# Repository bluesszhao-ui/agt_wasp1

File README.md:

# wasp1

wasp1 is a minimal single-core RV32I + Zicsr SoC project.

The hardware is implemented in synthesizable SystemVerilog and follows
Rocket Chip-like high-level module boundaries while using AHB-Lite as the SoC
interconnect.

## Baseline

```text
ISA: RV32I + Zicsr
Privilege: Machine mode only
MMU/TLB/PTW: none
RTL: SystemVerilog, .sv suffix
SoC bus: AHB-Lite
Core/cache internal interface: lightweight valid/ready request-response
Core plan: simple 3-stage pipeline
I-cache: direct-mapped, 16-byte line
D-cache: direct-mapped, 16-byte line, write-through
Debug target: RISC-V External Debug Spec 0.13.x / OpenOCD / GDB
Final debug probe: FT2232H-based external hardware debugger
Program storage: executable OTP
Compiler work: LLVM-based bare-metal wasp1 toolchain and BSP
```

## Top-Level Modules

```text
common
wasp1
tile
core
frontend
icache
dcache
bus
otp
sram
dma
debug
timer
intc
wdg
uart
i2c
gpio
llvm_s1
ftdi_debugger
```

Each hardware module owns its own `rtl/`, `tb/`, `filelists/`, `docs/`,
`build/`, `logs/`, `wave/`, and `Makefile` directories.
`ftdi_debugger` is not chip RTL; it owns the external FTDI debugger hardware,
OpenOCD, and board bring-up collateral.

## Current Status

Implemented and verified:

```text
common
bus
sram
otp
timer
gpio
uart
dma
intc
core
frontend
icache
dcache
tile
debug leaf blocks
wdg
i2c
wasp1 top integration smoke
```

Current residual scope:

```text
debug integration:
  true DPC/DCSR capture, single-step, breakpoints, abstract memory access

external debugger:
  FT2232H hardware debugger schematic/PCB, OpenOCD config, FPGA/board bring-up

software/toolchain:
  llvm_s1 BSP, linker script, startup code, runtime, examples, tests

full-system validation:
  interrupt-driven firmware, longer generated-image boot/DMA/programming
  regressions
```

See [ROADMAP.md](ROADMAP.md) for the live progress list and next steps.

## Quick Commands

Run all currently wired lint targets:

```sh
make lint
```

Run all currently wired module simulations:

```sh
make sim
```

Run common lint only:

```sh
make -C common lint
```

Generated build, log, and waveform outputs are ignored by git.

## Documentation

Start here:

```text
docs/index.md
```

Important project documents:

```text
ROADMAP.md
docs/wasp1_architecture.md
docs/wasp1_module_hierarchy.md
docs/wasp1_memory_map.md
docs/wasp1_design_plan.md
docs/wasp1_verification_plan.md
docs/wasp1_debug_strategy.md
docs/wasp1_otp_boot_strategy.md
docs/wasp1_llvm_s1_plan.md
docs/wasp1_implementation_targets.md
docs/wasp1_documentation_policy.md
docs/wasp1_omnigraffle_diagram_policy.md
```

## Contributor and Agent Rules

Human contributor guidance:

```text
CONTRIBUTING.md
```

Agent workflow rules:

```text
AGENTS.md
```

## License

wasp1 is licensed under the Apache License, Version 2.0. See [LICENSE](LICENSE).

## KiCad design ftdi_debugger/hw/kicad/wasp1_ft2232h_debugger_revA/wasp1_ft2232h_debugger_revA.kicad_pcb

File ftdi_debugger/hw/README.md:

# ftdi_debugger Hardware

This directory holds the FTDI debugger hardware collateral:

```text
schematic source
schematic PDF
PCB layout
gerbers
BOM
assembly notes
bring-up notes
```

The checked-in Rev A source package is:

```text
kicad/wasp1_ft2232h_debugger_revA/wasp1_ft2232h_debugger_revA.kicad_sch
schematic/wasp1_ft2232h_debugger_revA_schematic.md
schematic/wasp1_ft2232h_debugger_revA.pdf
schematic/svg/
netlist/wasp1_ft2232h_debugger_revA_nets.csv
bom/wasp1_ft2232h_debugger_revA_bom.csv
```

Its detailed electrical design and editable architecture diagram are:

```text
../docs/ftdi_debugger_revA_design_spec.md
../docs/diagrams/ftdi_debugger_revA_block.graffle
```

The native four-sheet KiCad hierarchy passes KiCad 10 ERC with zero errors and
zero warnings. The four-layer board is fully routed and its final DRC has zero
errors, zero unconnected pads, and zero schematic parity errors. Generated
manufacturing data remains under `build/manufacturing/`; fabrication and
assembly requirements are tracked in `fabrication/` and `assembly/`.

The PDF is a stable five-page A3 review preview assembled from individually
rendered sheets. The native KiCad hierarchy remains the electrical source of
truth; SVG exports provide vector page review.

The first schematic revision must follow:

```text
../docs/ftdi_debugger_pinout.md
../openocd/wasp1_ft2232h_reference.cfg
```

Before PCB work, keep the schematic pin mapping, target connector silk, and
OpenOCD layout masks synchronized. The repository-level static check is:

```text
make -C ftdi_debugger lint
```

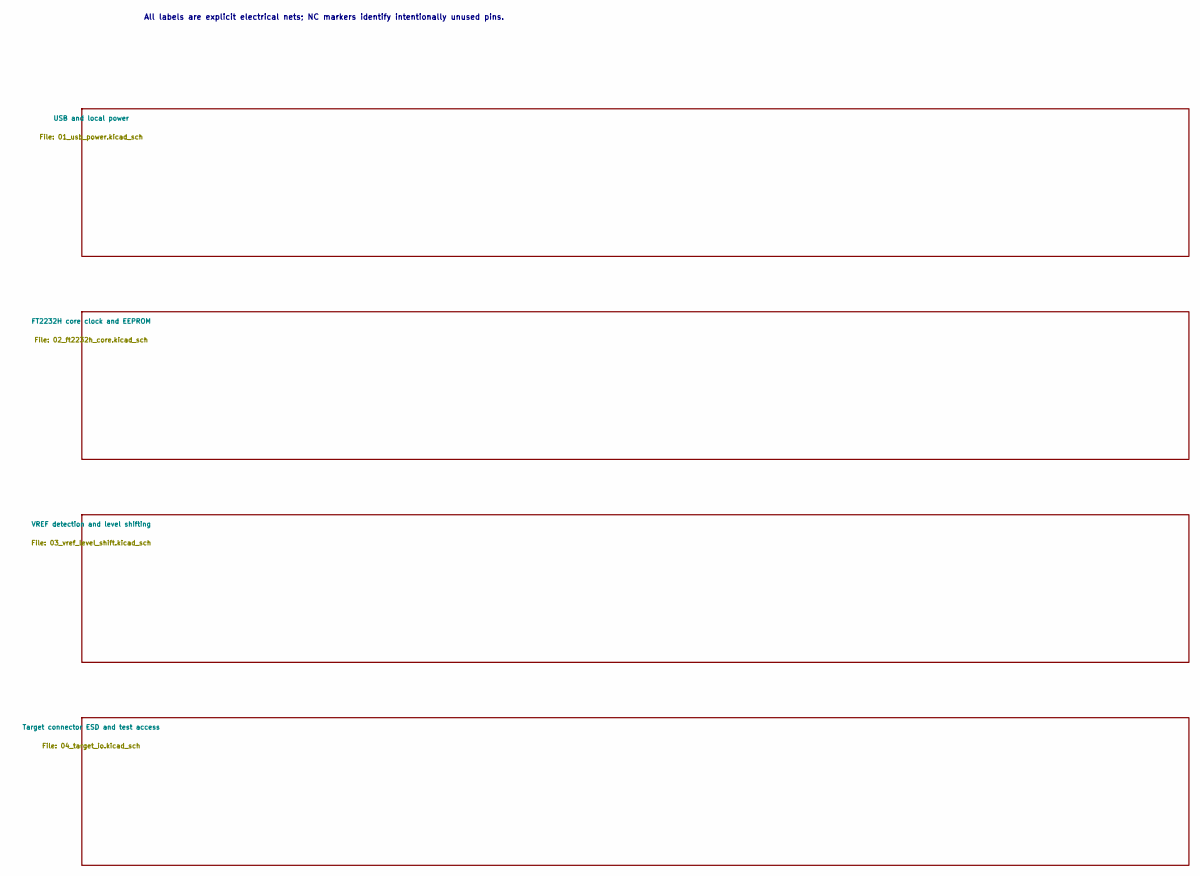
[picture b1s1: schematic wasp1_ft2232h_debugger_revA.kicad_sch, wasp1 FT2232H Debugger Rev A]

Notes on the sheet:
All labels are explicit electrical nets; NC markers identify intentionally unused pins.

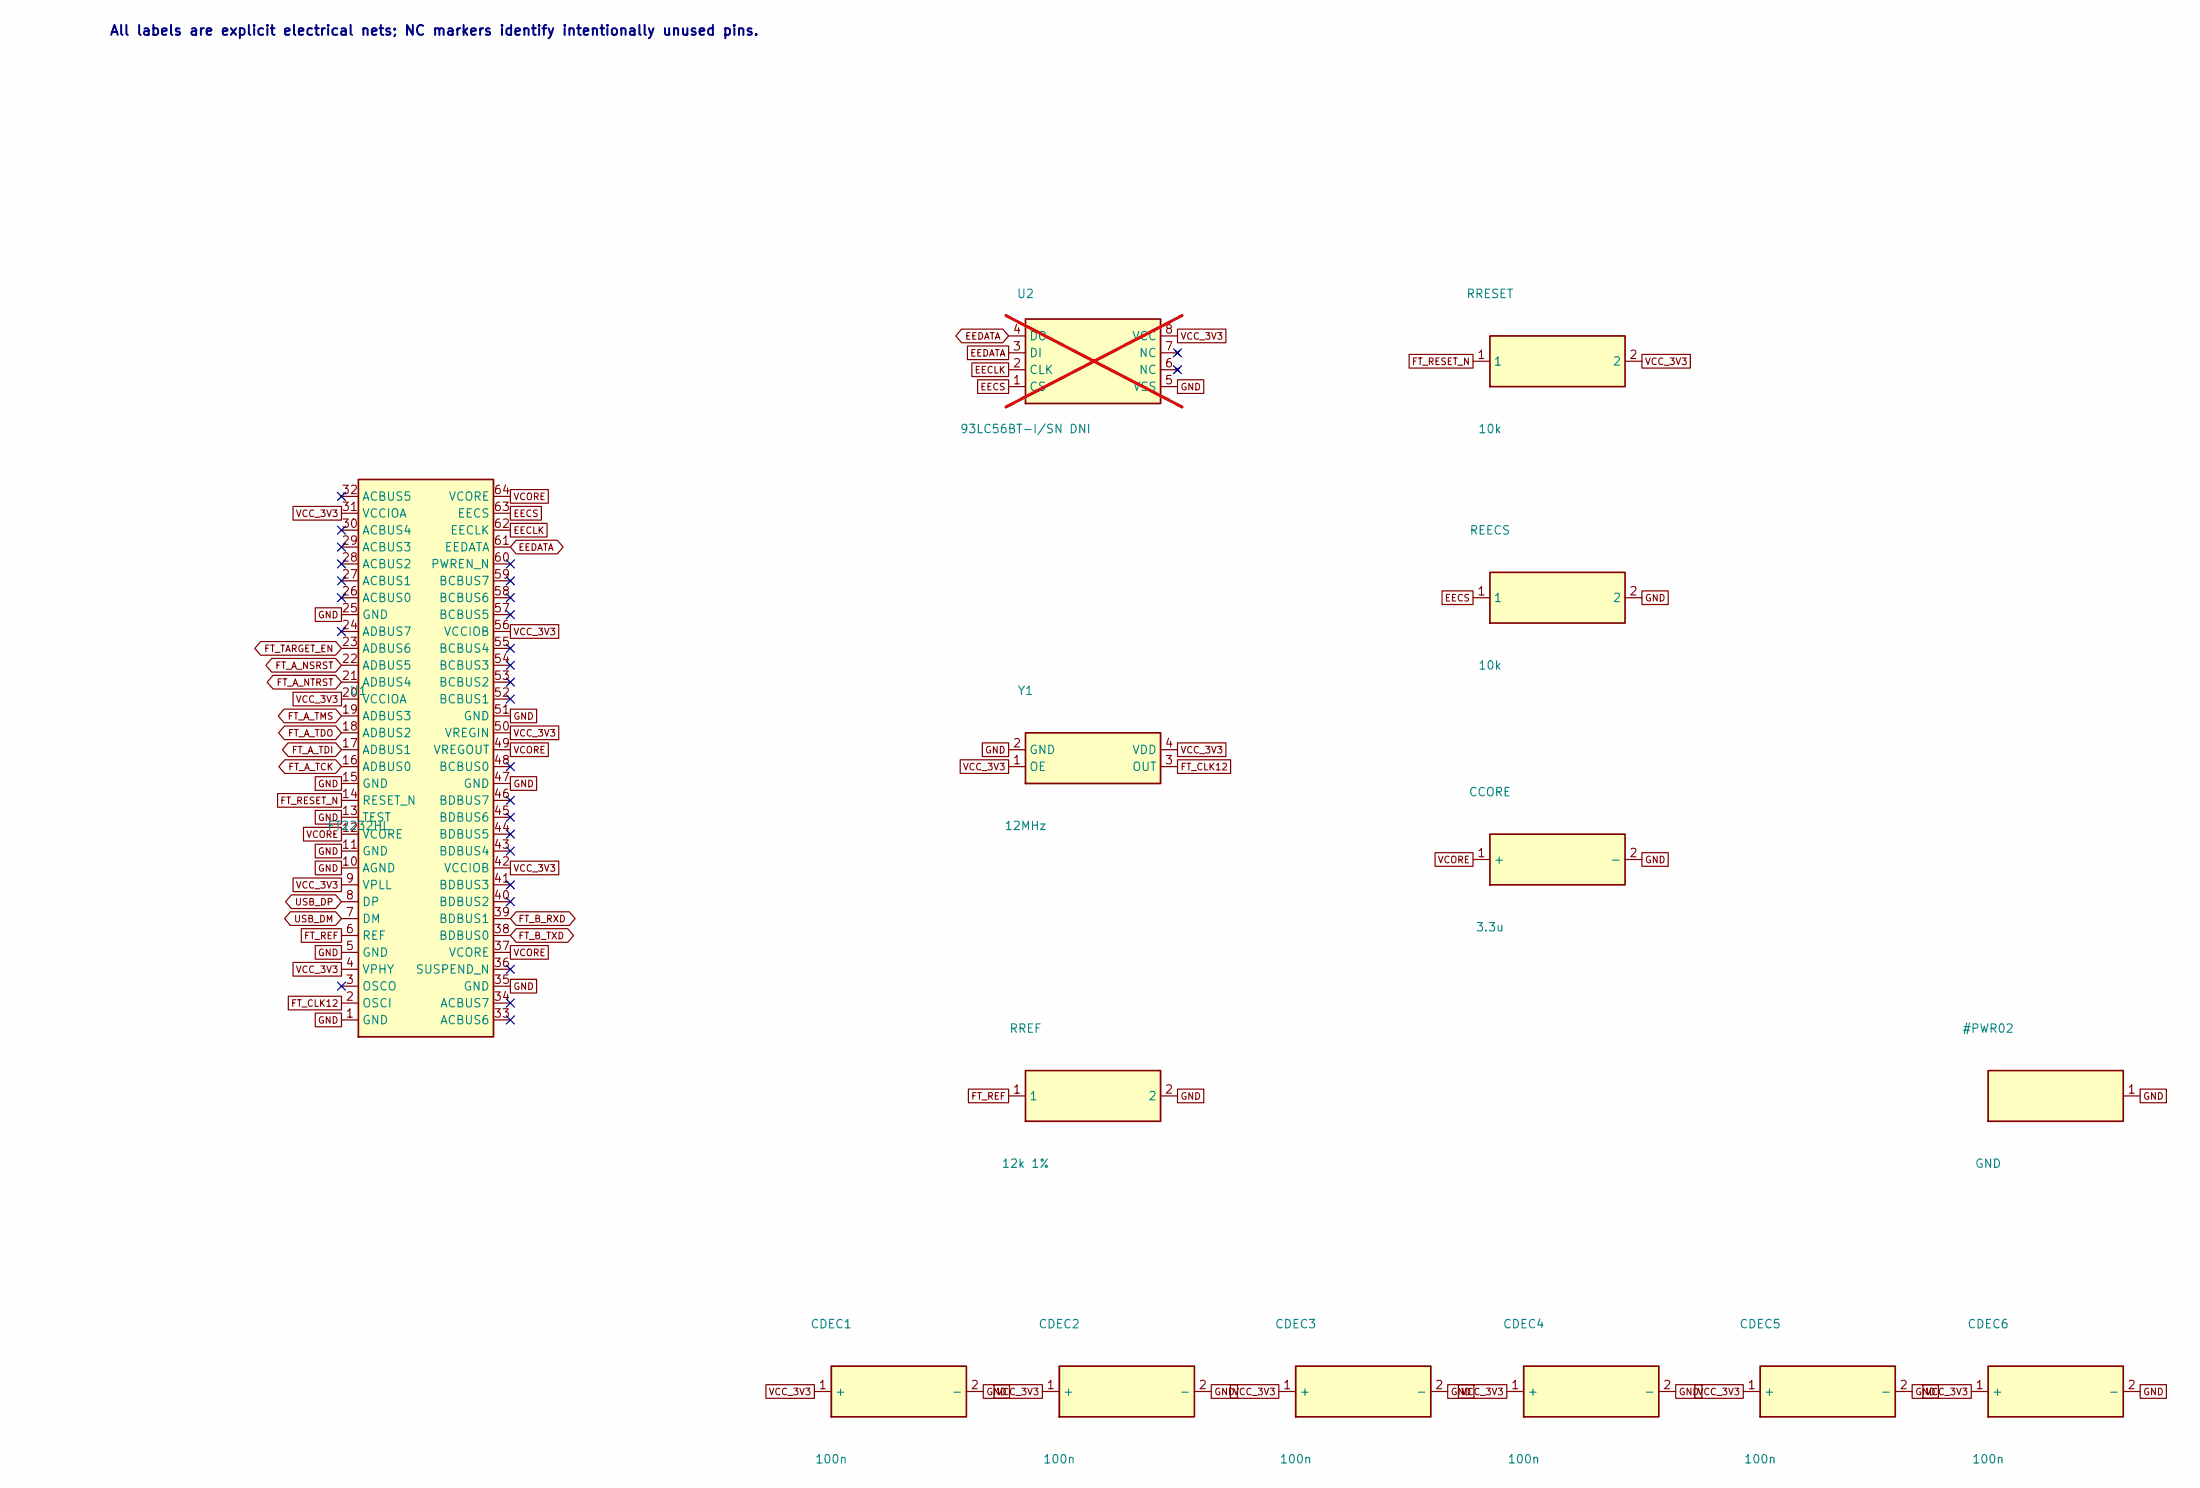
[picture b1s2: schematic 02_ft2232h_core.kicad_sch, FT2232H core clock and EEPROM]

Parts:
CCORE: 3.3u; C_0603_1608Metric
CDEC1, CDEC2, CDEC3, CDEC4, CDEC5, CDEC6: 100n; C_0402_1005Metric
REECS: 10k; R_0402_1005Metric
RREF: 12k 1%; R_0402_1005Metric
RRESET: 10k; R_0402_1005Metric
U1: FT2232HL; LQFP-64_10x10mm_P0.5mm
U2: 93LC56BT-I/SN DNI; SOIC-8_3.9x4.9mm_P1.27mm; not fitted
Y1: 12MHz; Oscillator_SMD_EuroQuartz_XO32-4Pin_3.2x2.5mm

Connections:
EECLK: U1.62 (EECLK), U2.2 (CLK)
EECS: REECS.1, U1.63 (EECS), U2.1 (CS)
EEDATA: U1.61 (EEDATA), U2.3 (DI), U2.4 (DO)
FT_A_NSRST: U1.22 (ADBUS5); also elsewhere on the board
FT_A_NTRST: U1.21 (ADBUS4); also elsewhere on the board
FT_A_TCK: U1.16 (ADBUS0); also elsewhere on the board
FT_A_TDI: U1.17 (ADBUS1); also elsewhere on the board
FT_A_TDO: U1.18 (ADBUS2); also elsewhere on the board
FT_A_TMS: U1.19 (ADBUS3); also elsewhere on the board
FT_B_RXD: U1.39 (BDBUS1); also elsewhere on the board
FT_B_TXD: U1.38 (BDBUS0); also elsewhere on the board
FT_CLK12: U1.2 (OSCI), Y1.3 (OUT)
FT_REF: RREF.1, U1.6 (REF)
FT_RESET_N: RRESET.1, U1.14 (RESET_N)
FT_TARGET_EN: U1.23 (ADBUS6); also elsewhere on the board
GND: CCORE.2 (-), CDEC1.2 (-), CDEC2.2 (-), CDEC3.2 (-), CDEC4.2 (-), CDEC5.2 (-), CDEC6.2 (-), REECS.2, RREF.2, U1.1 (GND), U1.5 (GND), U1.10 (AGND), U1.11 (GND), U1.13 (TEST), U1.15 (GND), U1.25 (GND), U1.35 (GND), U1.47 (GND), U1.51 (GND), U2.5 (VSS), Y1.2 (GND); also elsewhere on the board
USB_DM: U1.7 (DM); also elsewhere on the board
USB_DP: U1.8 (DP); also elsewhere on the board
VCC_3V3: CDEC1.1 (+), CDEC2.1 (+), CDEC3.1 (+), CDEC4.1 (+), CDEC5.1 (+), CDEC6.1 (+), RRESET.2, U1.4 (VPHY), U1.9 (VPLL), U1.20 (VCCIOA), U1.31 (VCCIOA), U1.42 (VCCIOB), U1.50 (VREGIN), U1.56 (VCCIOB), U2.8 (VCC), Y1.1 (OE), Y1.4 (VDD); also elsewhere on the board
VCORE: CCORE.1 (+), U1.12 (VCORE), U1.37 (VCORE), U1.49 (VREGOUT), U1.64 (VCORE); also elsewhere on the board

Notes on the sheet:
All labels are explicit electrical nets; NC markers identify intentionally unused pins.

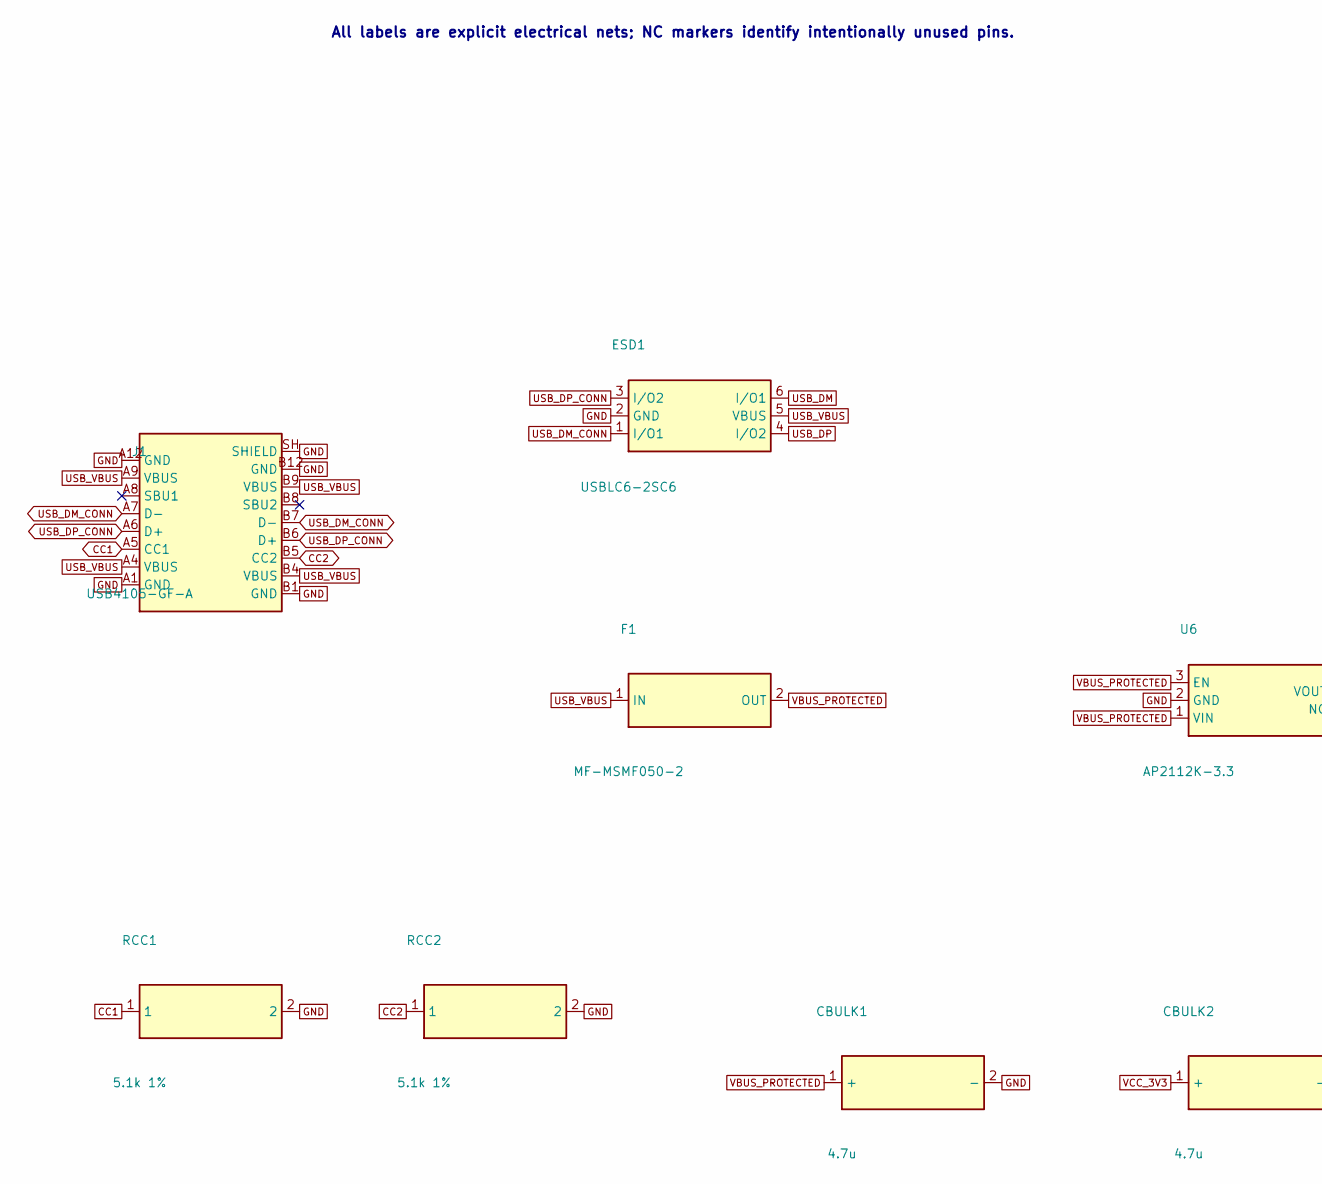
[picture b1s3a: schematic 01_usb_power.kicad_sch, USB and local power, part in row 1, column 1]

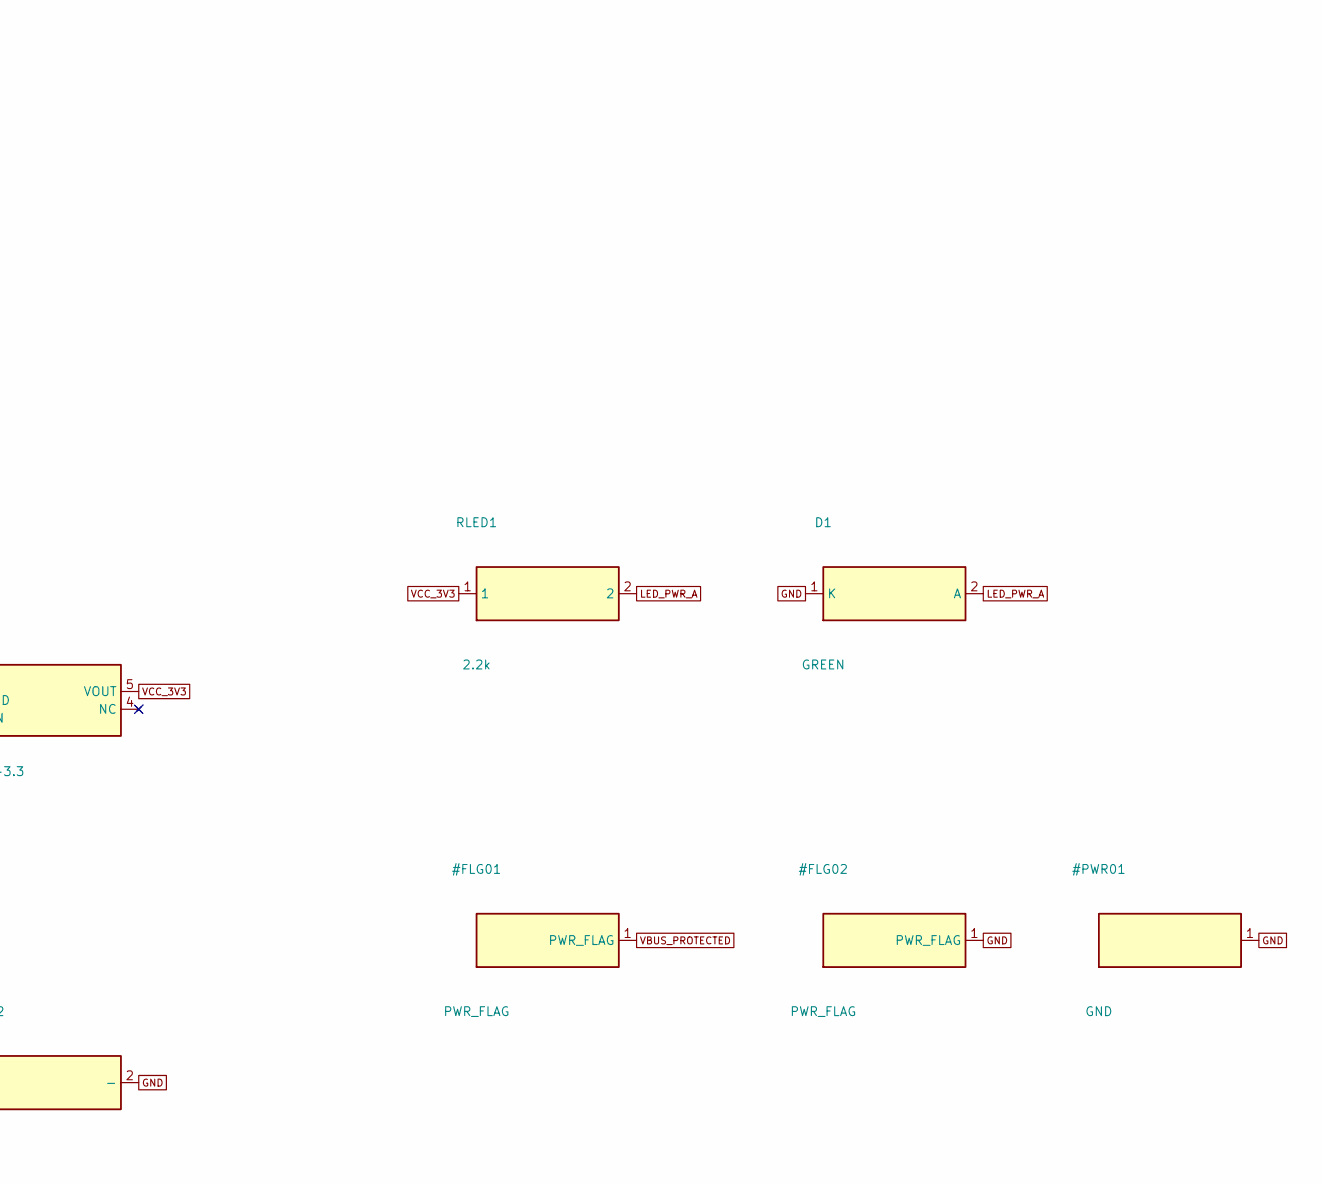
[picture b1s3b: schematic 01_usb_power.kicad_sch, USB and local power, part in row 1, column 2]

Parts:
CBULK1, CBULK2: 4.7u; C_0805_2012Metric
D1: GREEN; LED_0603_1608Metric
ESD1: USBLC6-2SC6; SOT-23-6
F1: MF-MSMF050-2; Fuse_1812_4532Metric
J1: USB4105-GF-A; USB_C_Receptacle_GCT_USB4105-xx-A_16P_TopMnt_Horizontal
RCC1, RCC2: 5.1k 1%; R_0402_1005Metric
RLED1: 2.2k; R_0402_1005Metric
U6: AP2112K-3.3; SOT-23-5

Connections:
CC1: J1.A5 (CC1), RCC1.1
CC2: J1.B5 (CC2), RCC2.1
GND: CBULK1.2 (-), CBULK2.2 (-), D1.1 (K), ESD1.2 (GND), J1.A1 (GND), J1.A12 (GND), J1.B1 (GND), J1.B12 (GND), J1.SH (SHIELD), RCC1.2, RCC2.2, U6.2 (GND); also elsewhere on the board
LED_PWR_A: D1.2 (A), RLED1.2
USB_DM: ESD1.6 (I/O1); also elsewhere on the board
USB_DM_CONN: ESD1.1 (I/O1), J1.A7 (D-), J1.B7 (D-)
USB_DP: ESD1.4 (I/O2); also elsewhere on the board
USB_DP_CONN: ESD1.3 (I/O2), J1.A6 (D+), J1.B6 (D+)
USB_VBUS: ESD1.5 (VBUS), F1.1 (IN), J1.A4 (VBUS), J1.A9 (VBUS), J1.B4 (VBUS), J1.B9 (VBUS)
VBUS_PROTECTED: CBULK1.1 (+), F1.2 (OUT), U6.1 (VIN), U6.3 (EN)
VCC_3V3: CBULK2.1 (+), RLED1.1, U6.5 (VOUT); also elsewhere on the board

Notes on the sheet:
All labels are explicit electrical nets; NC markers identify intentionally unused pins.

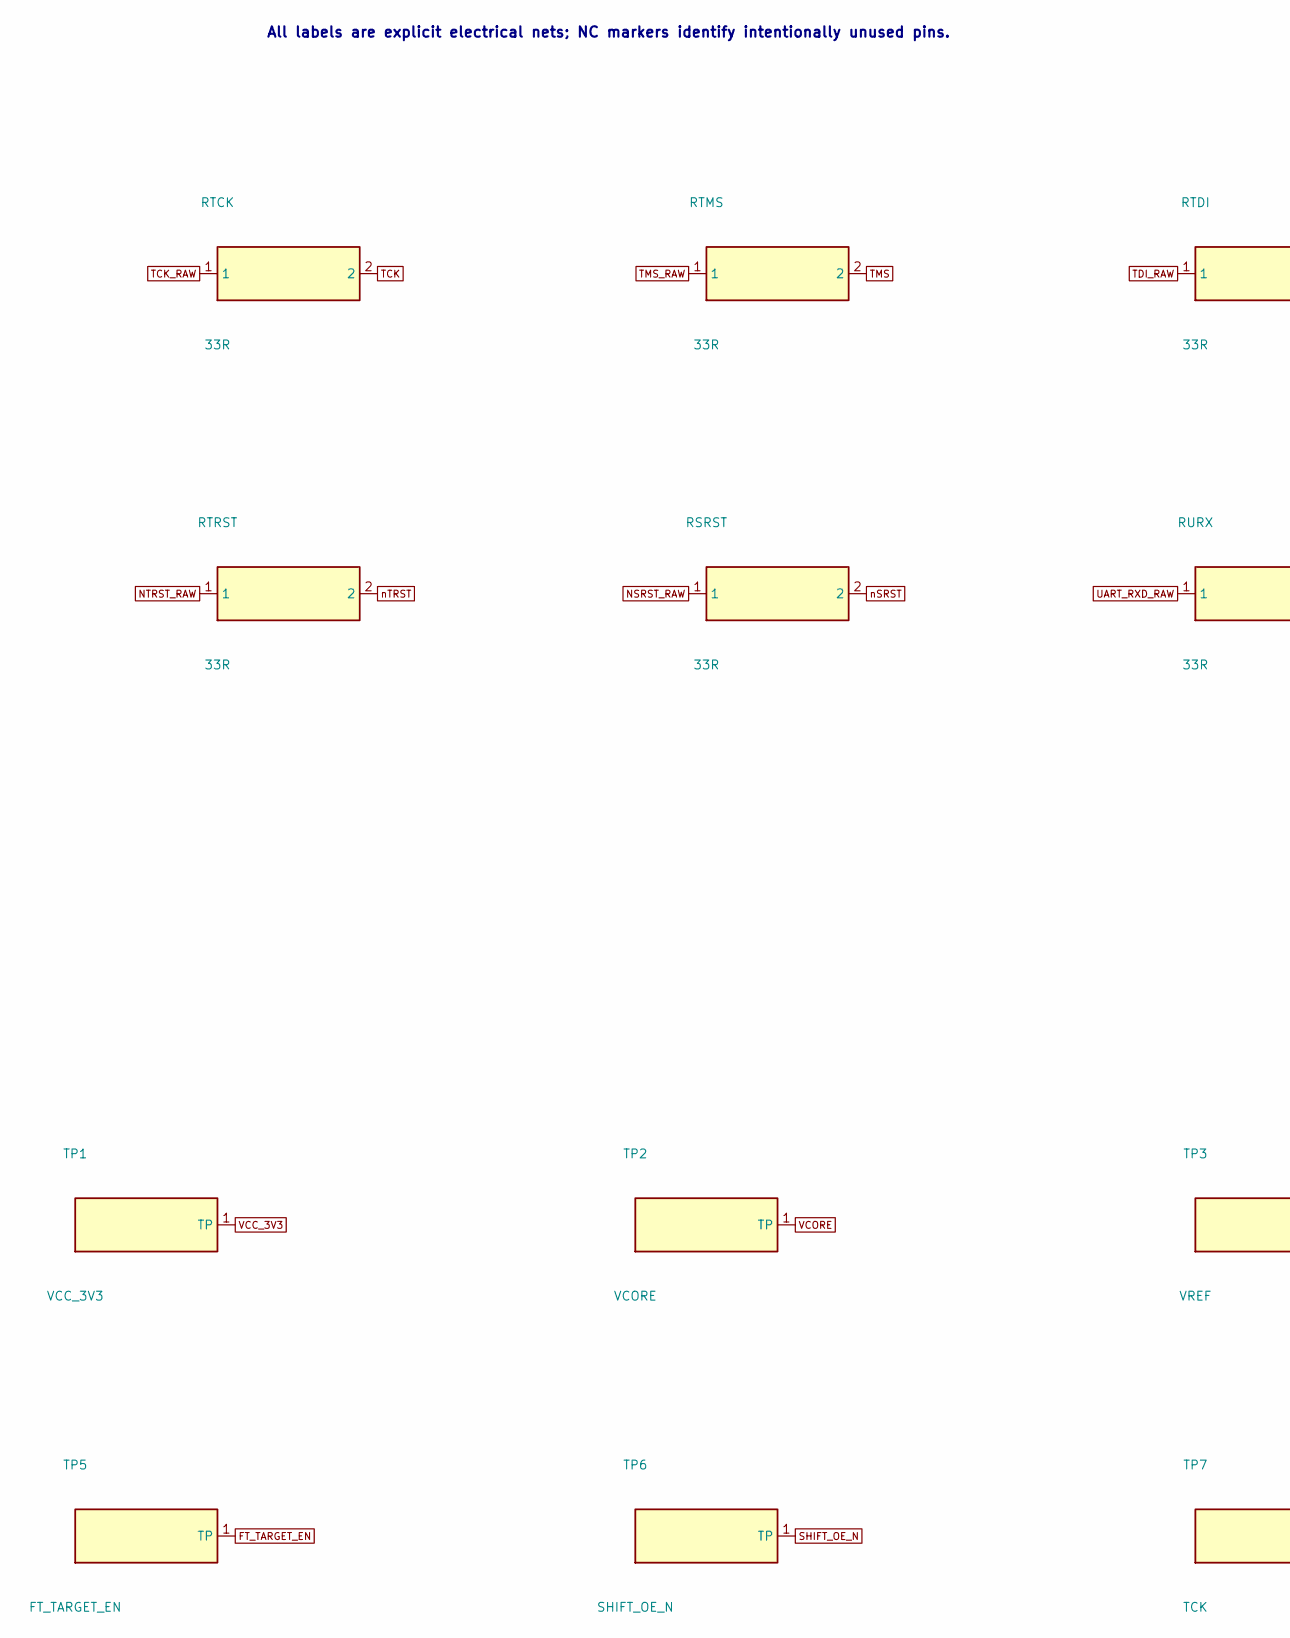
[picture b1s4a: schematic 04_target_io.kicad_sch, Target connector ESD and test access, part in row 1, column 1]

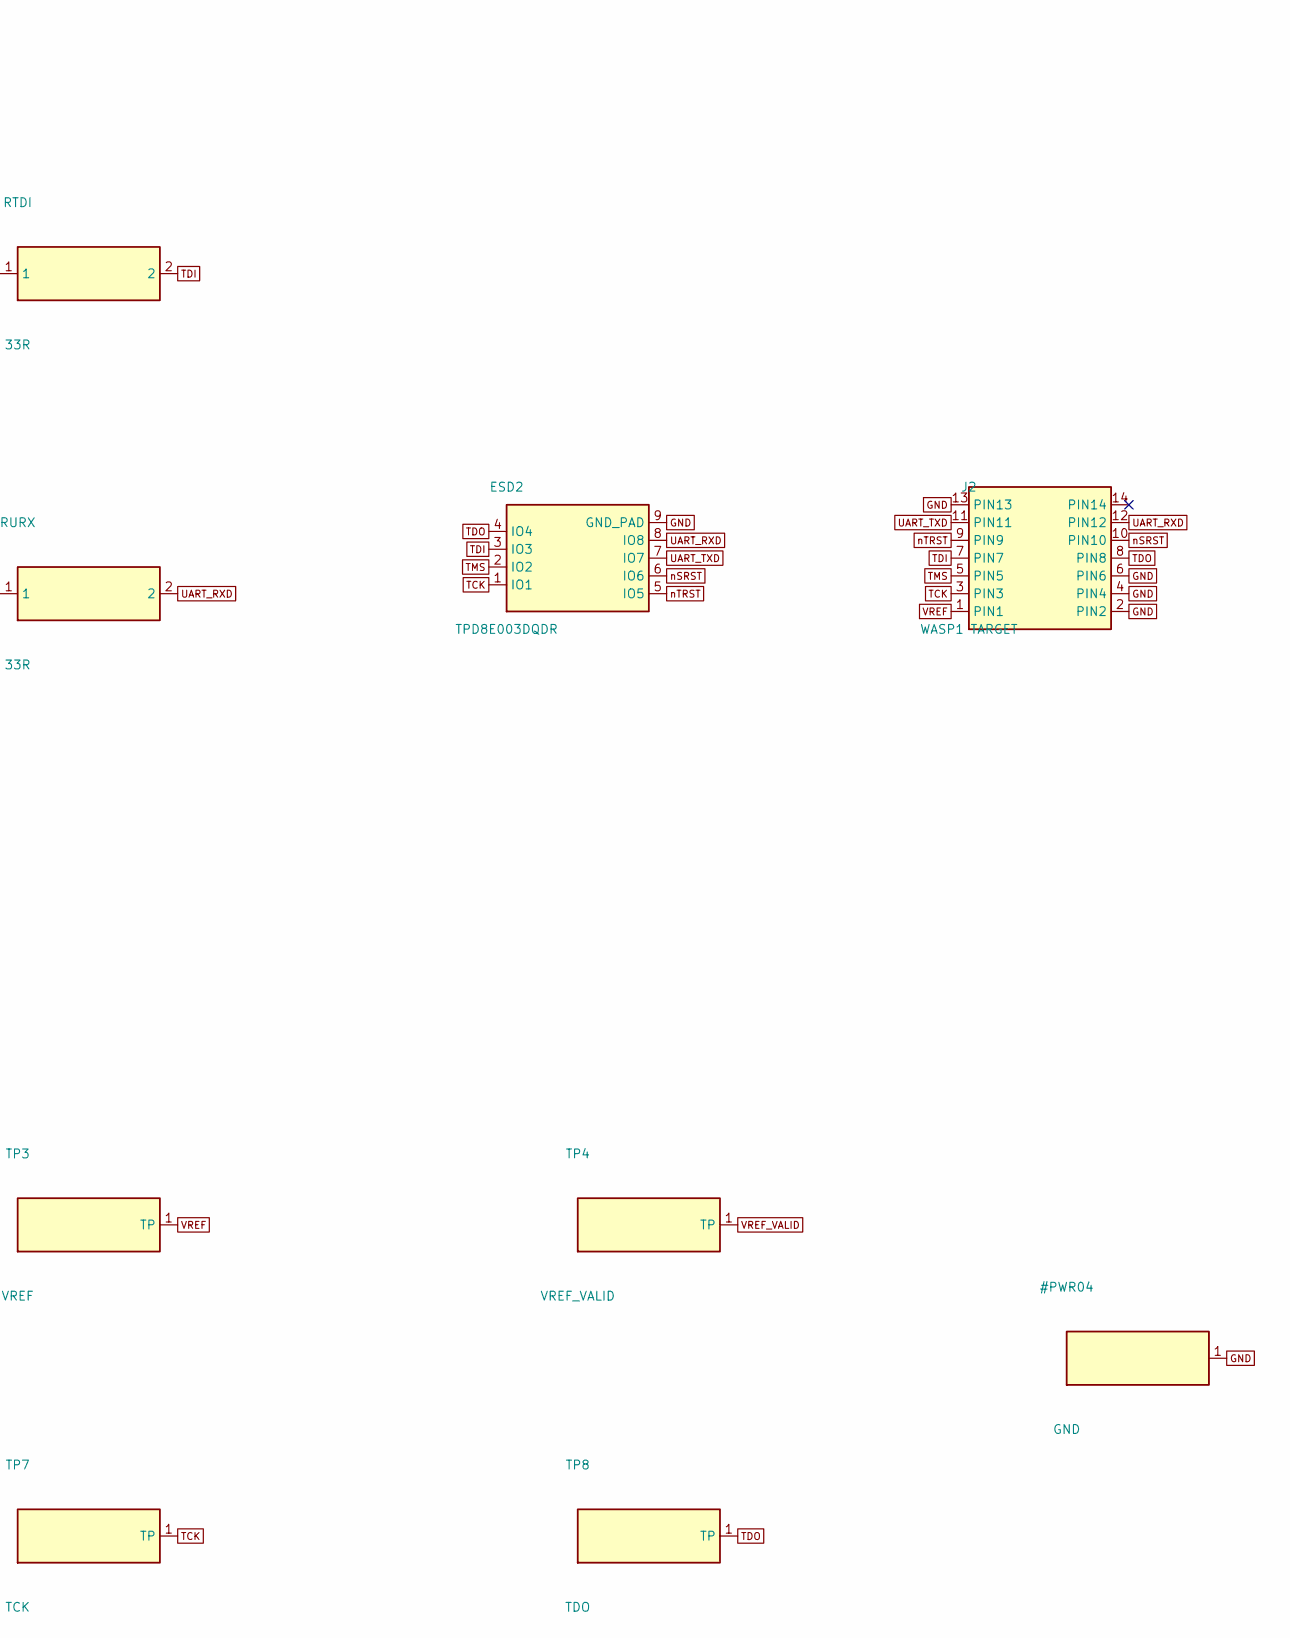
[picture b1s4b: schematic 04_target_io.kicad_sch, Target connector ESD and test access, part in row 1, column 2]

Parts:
ESD2: TPD8E003DQDR; WSON-8-1EP_2x2mm_P0.5mm_EP0.9x1.6mm
J2: WASP1 TARGET; IDC-Header_2x07_P2.54mm_Vertical
RSRST: 33R; R_0402_1005Metric
RTCK: 33R; R_0402_1005Metric
RTDI: 33R; R_0402_1005Metric
RTMS: 33R; R_0402_1005Metric
RTRST: 33R; R_0402_1005Metric
RURX: 33R; R_0402_1005Metric
TP1: VCC_3V3; TestPoint_Pad_D1.0mm
TP2: VCORE; TestPoint_Pad_D1.0mm
TP3: VREF; TestPoint_Pad_D1.0mm
TP4: VREF_VALID; TestPoint_Pad_D1.0mm
TP5: FT_TARGET_EN; TestPoint_Pad_D1.0mm
TP6: SHIFT_OE_N; TestPoint_Pad_D1.0mm
TP7: TCK; TestPoint_Pad_D1.0mm
TP8: TDO; TestPoint_Pad_D1.0mm

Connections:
FT_TARGET_EN: TP5.1; also elsewhere on the board
GND: ESD2.9 (GND_PAD), J2.2 (PIN2), J2.4 (PIN4), J2.6 (PIN6), J2.13 (PIN13); also elsewhere on the board
NSRST_RAW: RSRST.1; also elsewhere on the board
NTRST_RAW: RTRST.1; also elsewhere on the board
SHIFT_OE_N: TP6.1; also elsewhere on the board
TCK: ESD2.1 (IO1), J2.3 (PIN3), RTCK.2, TP7.1
TCK_RAW: RTCK.1; also elsewhere on the board
TDI: ESD2.3 (IO3), J2.7 (PIN7), RTDI.2
TDI_RAW: RTDI.1; also elsewhere on the board
TDO: ESD2.4 (IO4), J2.8 (PIN8), TP8.1; also elsewhere on the board
TMS: ESD2.2 (IO2), J2.5 (PIN5), RTMS.2
TMS_RAW: RTMS.1; also elsewhere on the board
UART_RXD: ESD2.8 (IO8), J2.12 (PIN12), RURX.2
UART_RXD_RAW: RURX.1; also elsewhere on the board
UART_TXD: ESD2.7 (IO7), J2.11 (PIN11); also elsewhere on the board
VCC_3V3: TP1.1; also elsewhere on the board
VCORE: TP2.1; also elsewhere on the board
VREF: J2.1 (PIN1), TP3.1; also elsewhere on the board
VREF_VALID: TP4.1; also elsewhere on the board
nSRST: ESD2.6 (IO6), J2.10 (PIN10), RSRST.2
nTRST: ESD2.5 (IO5), J2.9 (PIN9), RTRST.2

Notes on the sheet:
All labels are explicit electrical nets; NC markers identify intentionally unused pins.

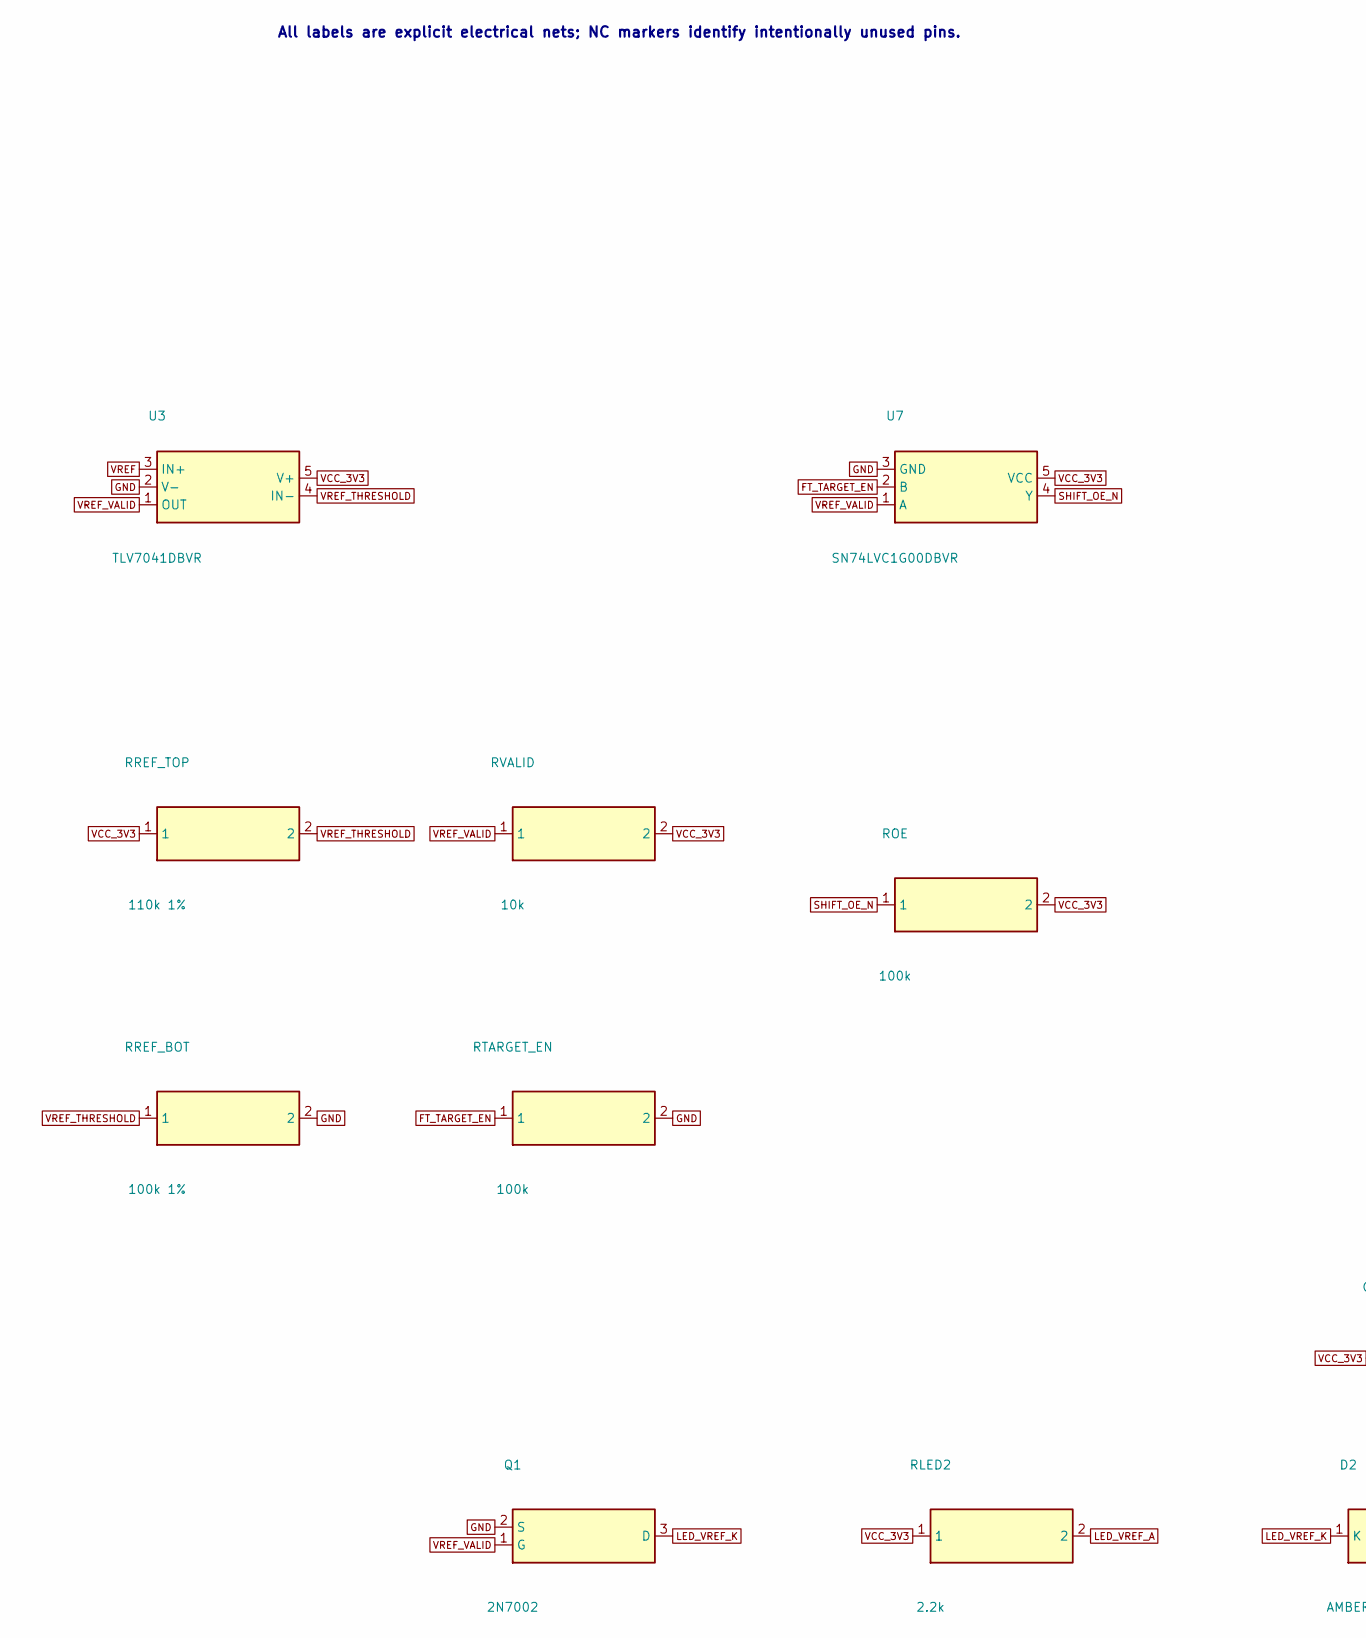
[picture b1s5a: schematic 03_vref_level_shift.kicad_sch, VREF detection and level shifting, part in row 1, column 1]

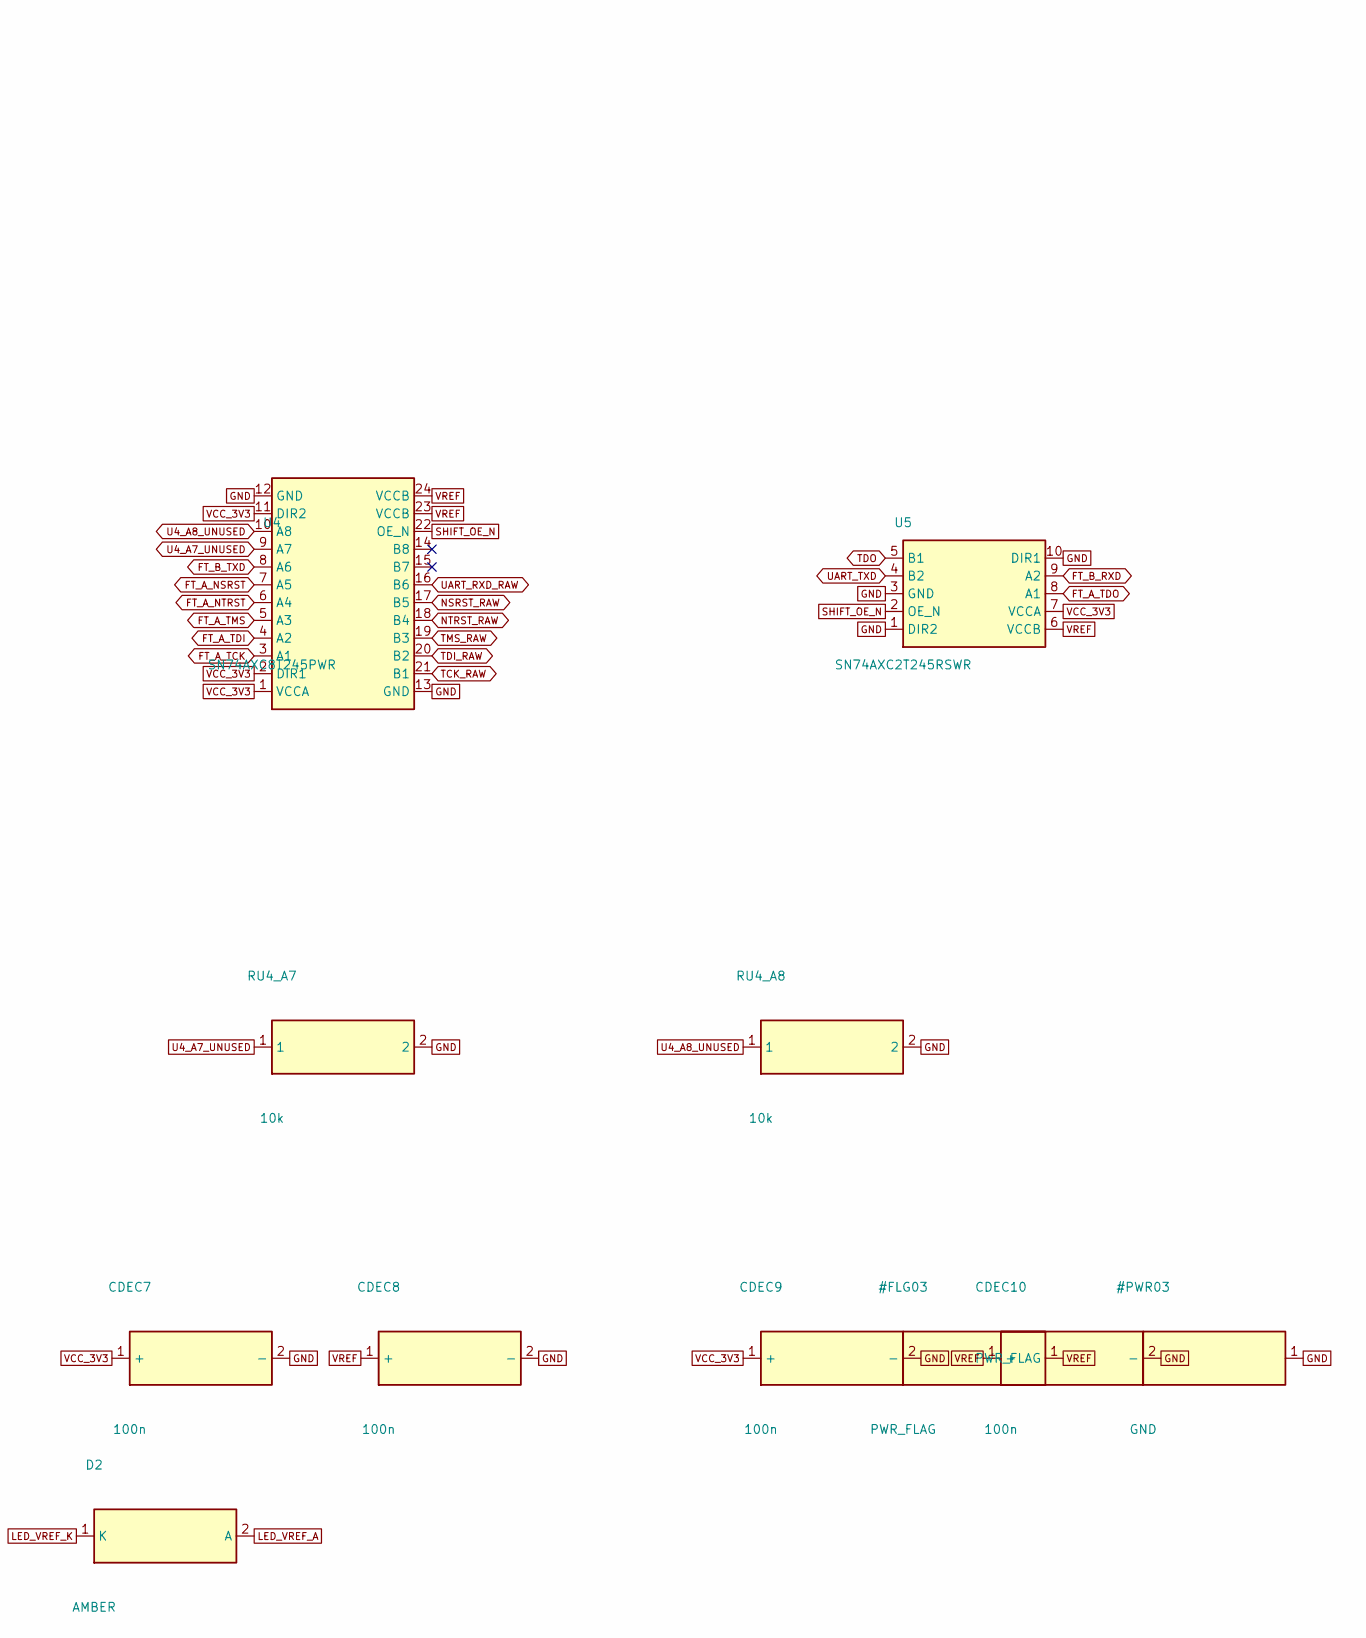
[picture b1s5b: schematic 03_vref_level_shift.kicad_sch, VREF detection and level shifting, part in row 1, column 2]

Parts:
CDEC7, CDEC8, CDEC9, CDEC10: 100n; C_0402_1005Metric
D2: AMBER; LED_0603_1608Metric
Q1: 2N7002; SOT-23
RLED2: 2.2k; R_0402_1005Metric
ROE: 100k; R_0402_1005Metric
RREF_BOT: 100k 1%; R_0402_1005Metric
RREF_TOP: 110k 1%; R_0402_1005Metric
RTARGET_EN: 100k; R_0402_1005Metric
RU4_A7, RU4_A8: 10k; R_0402_1005Metric
RVALID: 10k; R_0402_1005Metric
U3: TLV7041DBVR; SOT-23-5
U4: SN74AXC8T245PWR; TSSOP-24_4.4x7.8mm_P0.65mm
U5: SN74AXC2T245RSWR; Texas_RSW0010A_UQFN-10_1.4x1.8mm_P0.4mm
U7: SN74LVC1G00DBVR; SOT-23-5

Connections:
FT_A_NSRST: U4.7 (A5); also elsewhere on the board
FT_A_NTRST: U4.6 (A4); also elsewhere on the board
FT_A_TCK: U4.3 (A1); also elsewhere on the board
FT_A_TDI: U4.4 (A2); also elsewhere on the board
FT_A_TDO: U5.8 (A1); also elsewhere on the board
FT_A_TMS: U4.5 (A3); also elsewhere on the board
FT_B_RXD: U5.9 (A2); also elsewhere on the board
FT_B_TXD: U4.8 (A6); also elsewhere on the board
FT_TARGET_EN: RTARGET_EN.1, U7.2 (B); also elsewhere on the board
GND: CDEC7.2 (-), CDEC8.2 (-), CDEC9.2 (-), CDEC10.2 (-), Q1.2 (S), RREF_BOT.2, RTARGET_EN.2, RU4_A7.2, RU4_A8.2, U3.2 (V-), U4.12 (GND), U4.13 (GND), U5.1 (DIR2), U5.3 (GND), U5.10 (DIR1), U7.3 (GND); also elsewhere on the board
LED_VREF_A: D2.2 (A), RLED2.2
LED_VREF_K: D2.1 (K), Q1.3 (D)
NSRST_RAW: U4.17 (B5); also elsewhere on the board
NTRST_RAW: U4.18 (B4); also elsewhere on the board
SHIFT_OE_N: ROE.1, U4.22 (OE_N), U5.2 (OE_N), U7.4 (Y); also elsewhere on the board
TCK_RAW: U4.21 (B1); also elsewhere on the board
TDI_RAW: U4.20 (B2); also elsewhere on the board
TDO: U5.5 (B1); also elsewhere on the board
TMS_RAW: U4.19 (B3); also elsewhere on the board
U4_A7_UNUSED: RU4_A7.1, U4.9 (A7)
U4_A8_UNUSED: RU4_A8.1, U4.10 (A8)
UART_RXD_RAW: U4.16 (B6); also elsewhere on the board
UART_TXD: U5.4 (B2); also elsewhere on the board
VCC_3V3: CDEC7.1 (+), CDEC9.1 (+), RLED2.1, ROE.2, RREF_TOP.1, RVALID.2, U3.5 (V+), U4.1 (VCCA), U4.2 (DIR1), U4.11 (DIR2), U5.7 (VCCA), U7.5 (VCC); also elsewhere on the board
VREF: CDEC8.1 (+), CDEC10.1 (+), U3.3 (IN+), U4.23 (VCCB), U4.24 (VCCB), U5.6 (VCCB); also elsewhere on the board
VREF_THRESHOLD: RREF_BOT.1, RREF_TOP.2, U3.4 (IN-)
VREF_VALID: Q1.1 (G), RVALID.1, U3.1 (OUT), U7.1 (A); also elsewhere on the board

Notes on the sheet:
All labels are explicit electrical nets; NC markers identify intentionally unused pins.
